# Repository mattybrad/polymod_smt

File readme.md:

# PolyMod SMT test

This will be a small polyphonic digital modular synthesizer, using a Teensy 3.2. The design is based on my tutorial from Hackspace magazine (issue 17), and was also featured in the Book of Making (volume 2). Currently this is a work in progress, so don't go ordering any PCBs just yet. This is really just a project for me to get some practice designing with surface-mount components and specifying for a pick-and-place machine, which I haven't done before.

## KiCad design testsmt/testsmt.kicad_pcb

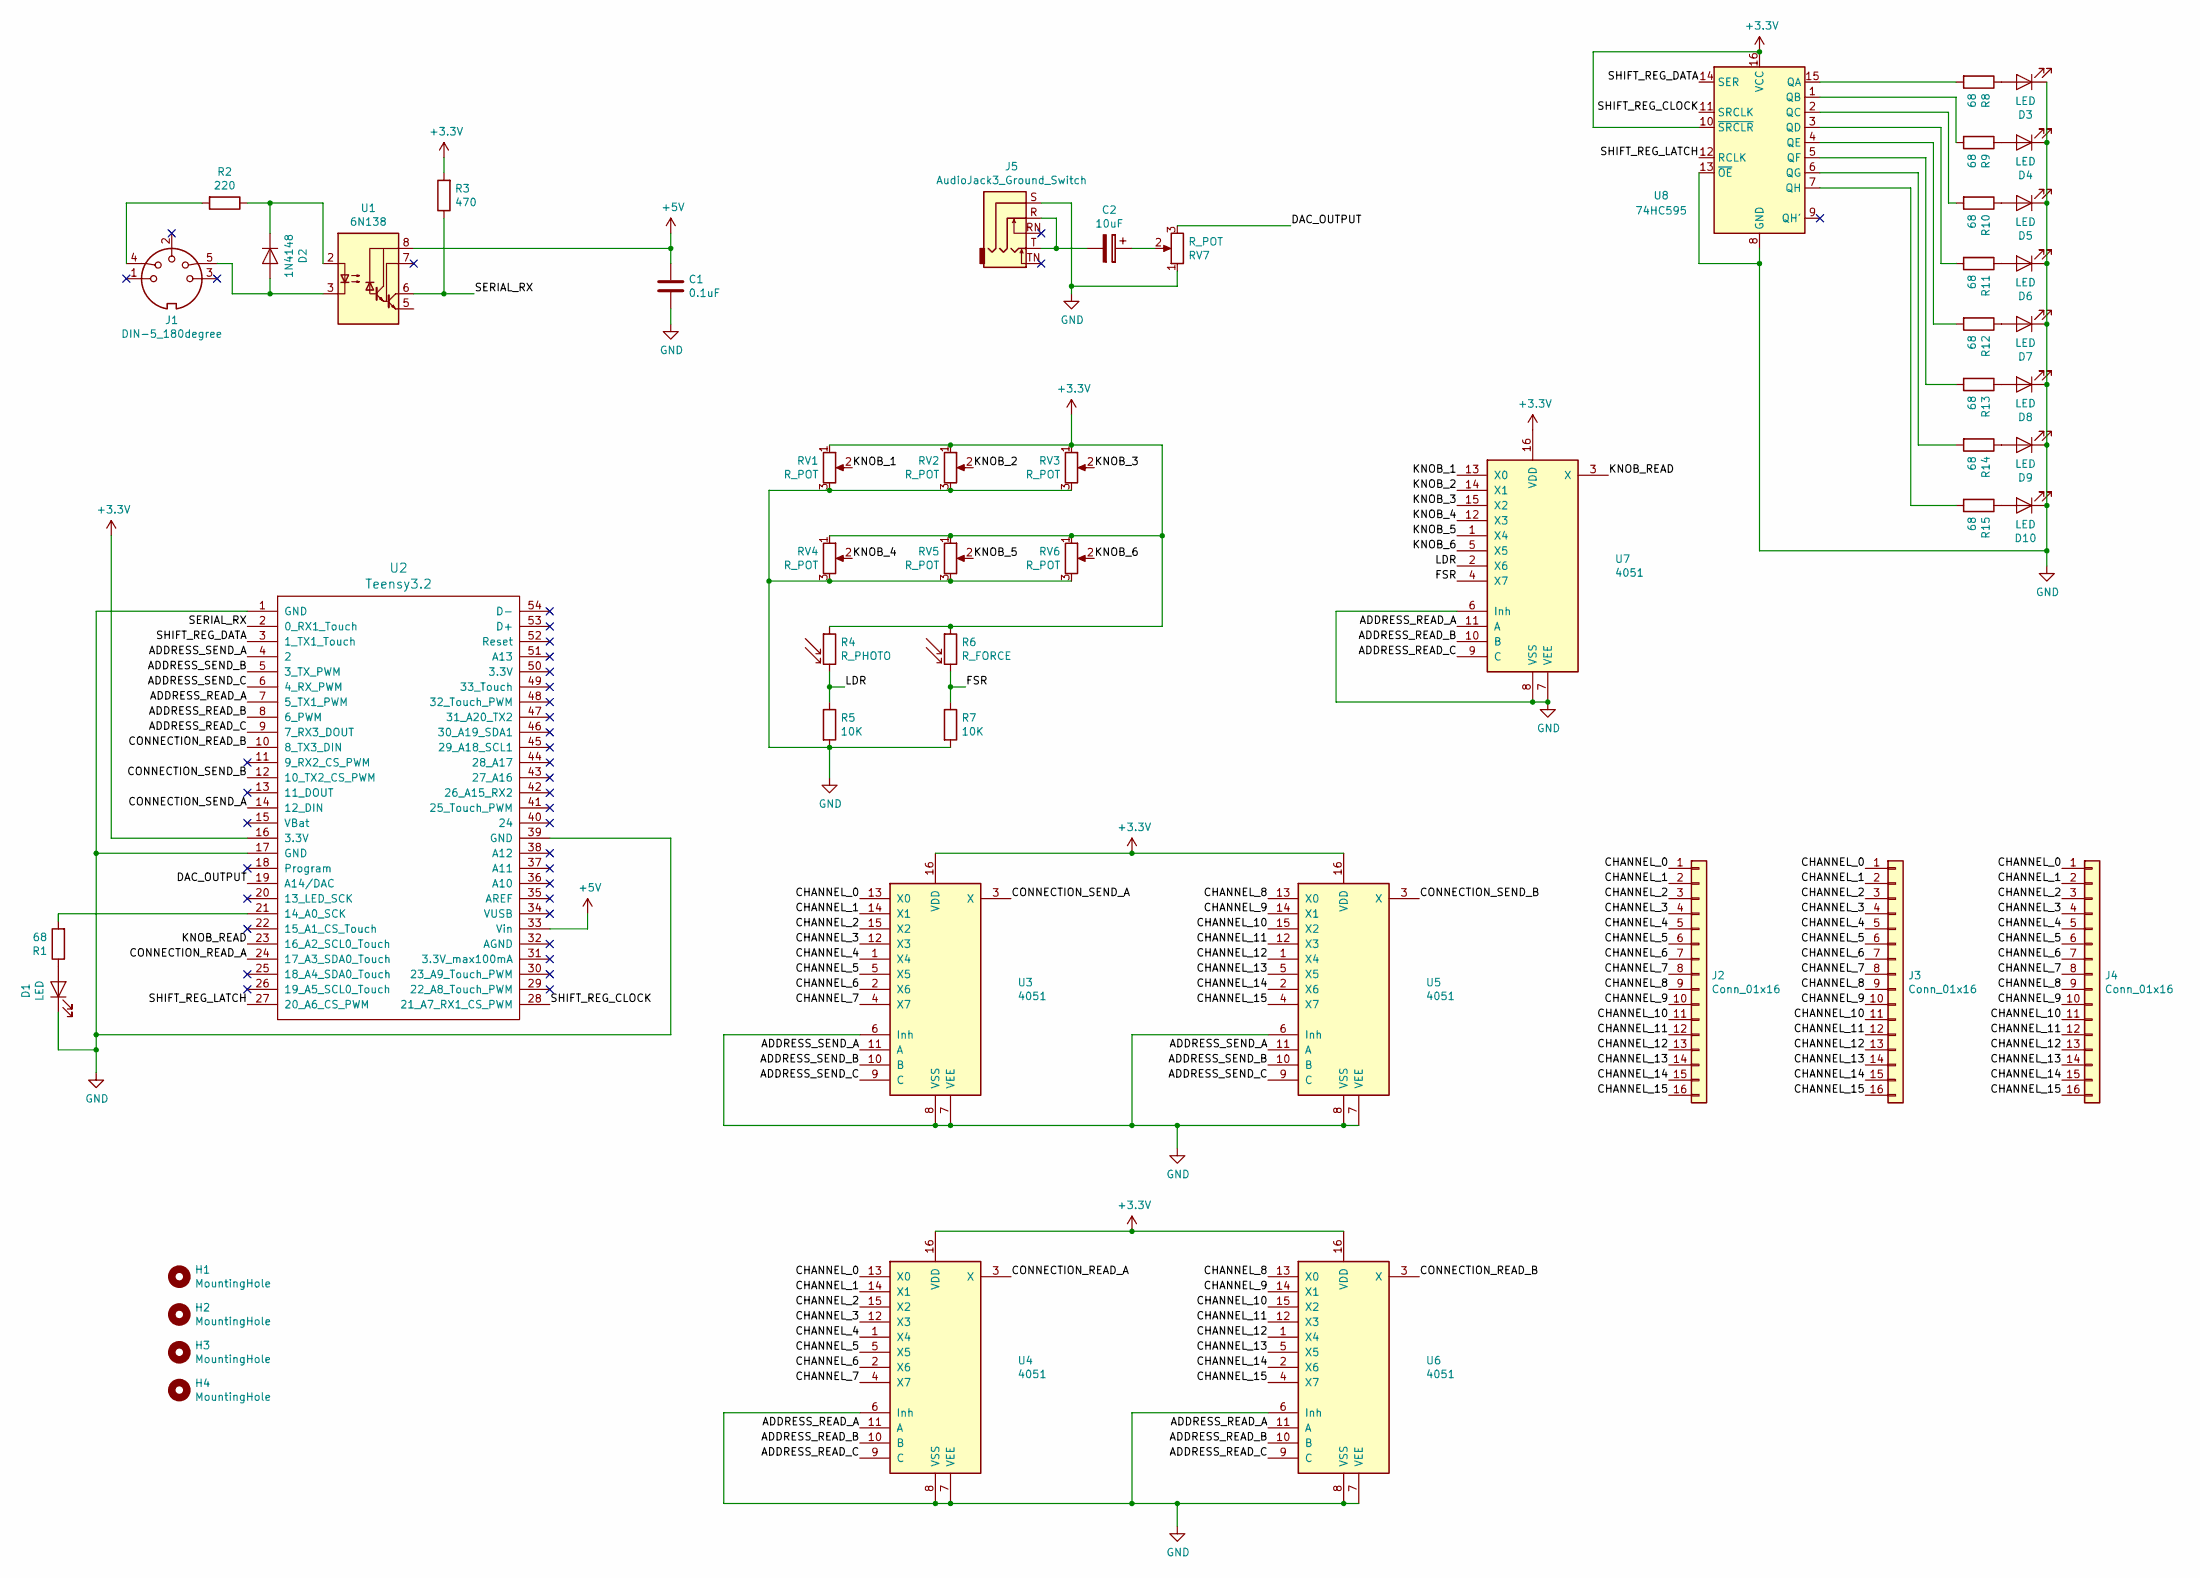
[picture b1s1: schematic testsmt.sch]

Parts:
C1: 0.1uF; C_0805_2012Metric
C2: 10uF; CP_EIA-3216-18_Kemet-A
D1, D3, D4, D5, D6, D7, D8, D9, D10: LED; LED_0805_2012Metric
D2: 1N4148; D_SOD-123
H1, H2, H3, H4: MountingHole; MountingHole_3.2mm_M3
J1: DIN-5_180degree; MIDI_DIN5
J2, J3, J4: Conn_01x16; PinSocket_1x16_P2.54mm_Vertical
J5: AudioJack3_Ground_Switch; Tayda_3.5mm_stereo_TRS_jack_A-853
R1, R8, R9, R10, R11, R12, R13, R14, R15: 68; R_0805_2012Metric
R2: 220; R_0805_2012Metric
R3: 470; R_0805_2012Metric
R4: R_PHOTO; PinHeader_1x02_P2.54mm_Vertical
R5, R7: 10K; R_0805_2012Metric
R6: R_FORCE; PinHeader_1x02_P2.54mm_Vertical
RV1, RV2, RV3, RV4, RV5, RV6, RV7: R_POT; Potentiometer_Alps_RK09K_Single_Vertical
U1: 6N138; SMDIP-8_W9.53mm
U2: Teensy3.2; Teensy30_31_32_LC
U3, U4, U5, U6, U7: 4051; SOIC-16_3.9x9.9mm_P1.27mm
U8: 74HC595; SOIC-16_3.9x9.9mm_P1.27mm

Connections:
+3V3: R3.2, R4.1, R6.1, RV1.1, RV2.1, RV3.1, RV4.1, RV5.1, RV6.1, U2.16 (3.3V), U3.16 (VDD), U4.16 (VDD), U5.16 (VDD), U6.16 (VDD), U7.16 (VDD), U8.10 (~SRCLR), U8.16 (VCC)
+5V: C1.1, U1.8 (VCC), U2.33 (Vin)
/ADDRESS_READ_A: U2.7 (5_TX1_PWM), U4.11 (A), U6.11 (A), U7.11 (A)
/ADDRESS_READ_B: U2.8 (6_PWM), U4.10 (B), U6.10 (B), U7.10 (B)
/ADDRESS_READ_C: U2.9 (7_RX3_DOUT), U4.9 (C), U6.9 (C), U7.9 (C)
/ADDRESS_SEND_A: U2.4 (2), U3.11 (A), U5.11 (A)
/ADDRESS_SEND_B: U2.5 (3_TX_PWM), U3.10 (B), U5.10 (B)
/ADDRESS_SEND_C: U2.6 (4_RX_PWM), U3.9 (C), U5.9 (C)
/CHANNEL_0: J2.1, J3.1, J4.1, U3.13 (X0), U4.13 (X0)
/CHANNEL_1: J2.2, J3.2, J4.2, U3.14 (X1), U4.14 (X1)
/CHANNEL_2: J2.3, J3.3, J4.3, U3.15 (X2), U4.15 (X2)
/CHANNEL_3: J2.4, J3.4, J4.4, U3.12 (X3), U4.12 (X3)
/CHANNEL_4: J2.5, J3.5, J4.5, U3.1 (X4), U4.1 (X4)
/CHANNEL_5: J2.6, J3.6, J4.6, U3.5 (X5), U4.5 (X5)
/CHANNEL_6: J2.7, J3.7, J4.7, U3.2 (X6), U4.2 (X6)
/CHANNEL_7: J2.8, J3.8, J4.8, U3.4 (X7), U4.4 (X7)
/CHANNEL_8: J2.9, J3.9, J4.9, U5.13 (X0), U6.13 (X0)
/CHANNEL_9: J2.10, J3.10, J4.10, U5.14 (X1), U6.14 (X1)
/CHANNEL_10: J2.11, J3.11, J4.11, U5.15 (X2), U6.15 (X2)
/CHANNEL_11: J2.12, J3.12, J4.12, U5.12 (X3), U6.12 (X3)
/CHANNEL_12: J2.13, J3.13, J4.13, U5.1 (X4), U6.1 (X4)
/CHANNEL_13: J2.14, J3.14, J4.14, U5.5 (X5), U6.5 (X5)
/CHANNEL_14: J2.15, J3.15, J4.15, U5.2 (X6), U6.2 (X6)
/CHANNEL_15: J2.16, J3.16, J4.16, U5.4 (X7), U6.4 (X7)
/CONNECTION_READ_A: U2.24 (17_A3_SDA0_Touch), U4.3 (X)
/CONNECTION_READ_B: U2.10 (8_TX3_DIN), U6.3 (X)
/CONNECTION_SEND_A: U2.14 (12_DIN), U3.3 (X)
/CONNECTION_SEND_B: U2.12 (10_TX2_CS_PWM), U5.3 (X)
/DAC_OUTPUT: RV7.3, U2.19 (A14/DAC)
/FSR: R6.2, R7.1, U7.4 (X7)
/KNOB_1: RV1.2, U7.13 (X0)
/KNOB_2: RV2.2, U7.14 (X1)
/KNOB_3: RV3.2, U7.15 (X2)
/KNOB_4: RV4.2, U7.12 (X3)
/KNOB_5: RV5.2, U7.1 (X4)
/KNOB_6: RV6.2, U7.5 (X5)
/KNOB_READ: U2.23 (16_A2_SCL0_Touch), U7.3 (X)
/LDR: R4.2, R5.1, U7.2 (X6)
/SERIAL_RX: R3.1, U1.6 (VO2), U2.2 (0_RX1_Touch)
/SHIFT_REG_CLOCK: U2.28 (21_A7_RX1_CS_PWM), U8.11 (SRCLK)
/SHIFT_REG_DATA: U2.3 (1_TX1_Touch), U8.14 (SER)
/SHIFT_REG_LATCH: U2.27 (20_A6_CS_PWM), U8.12 (RCLK)
GND: C1.2, D1.1 (K), D3.1 (K), D4.1 (K), D5.1 (K), D6.1 (K), D7.1 (K), D8.1 (K), D9.1 (K), D10.1 (K), J5.S, R5.2, R7.2, RV1.3, RV2.3, RV3.3, RV4.3, RV5.3, RV6.3, RV7.1, U2.1 (GND), U2.17 (GND), U2.39 (GND), U3.6 (Inh), U3.7 (VEE), U3.8 (VSS), U4.6 (Inh), U4.7 (VEE), U4.8 (VSS), U5.6 (Inh), U5.7 (VEE), U5.8 (VSS), U6.6 (Inh), U6.7 (VEE), U6.8 (VSS), U7.6 (Inh), U7.7 (VEE), U7.8 (VSS), U8.8 (GND), U8.13 (~OE)
unnamed: C2.1, RV7.2
unnamed: C2.2, J5.R, J5.T
unnamed: D1.2 (A), R1.1
unnamed: D2.1 (K), R2.1, U1.2 (C1)
unnamed: D2.2 (A), J1.5, U1.3 (C2)
unnamed: D3.2 (A), R8.1
unnamed: D4.2 (A), R9.1
unnamed: D5.2 (A), R10.1
unnamed: D6.2 (A), R11.1
unnamed: D7.2 (A), R12.1
unnamed: D8.2 (A), R13.1
unnamed: D9.2 (A), R14.1
unnamed: D10.2 (A), R15.1
unnamed: J1.4, R2.2
unnamed: R1.2, U2.21 (14_A0_SCK)
unnamed: R8.2, U8.15 (QA)
unnamed: R9.2, U8.1 (QB)
unnamed: R10.2, U8.2 (QC)
unnamed: R11.2, U8.3 (QD)
unnamed: R12.2, U8.4 (QE)
unnamed: R13.2, U8.5 (QF)
unnamed: R14.2, U8.6 (QG)
unnamed: R15.2, U8.7 (QH)

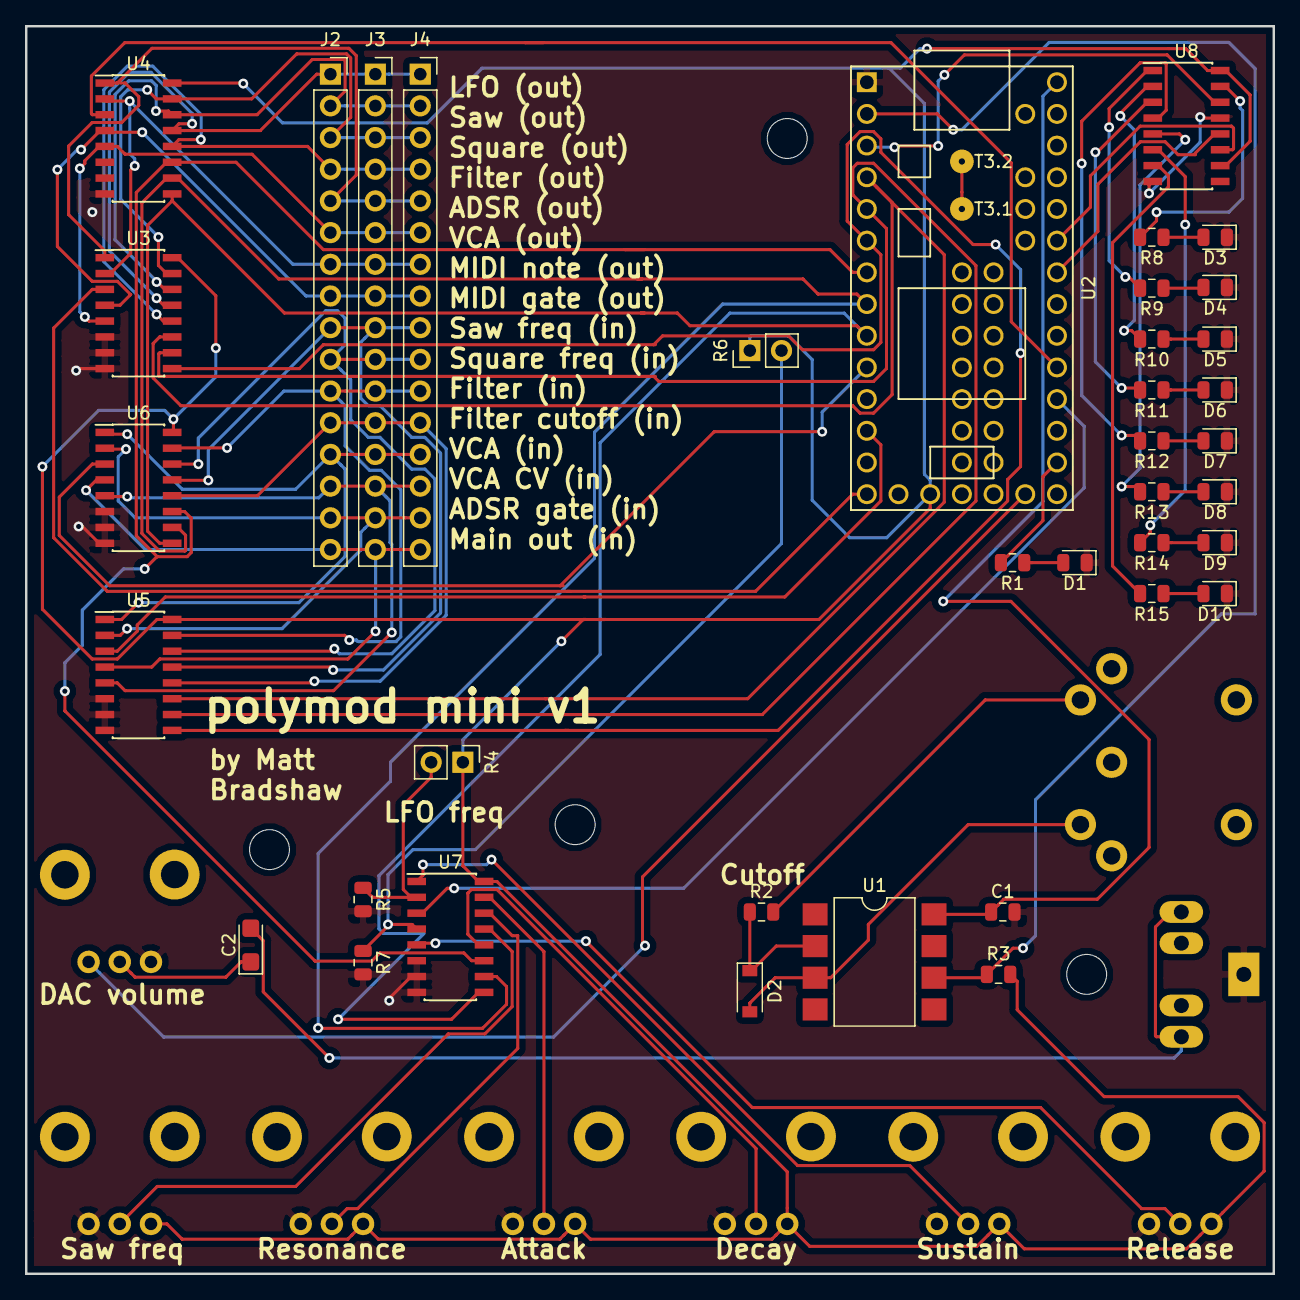
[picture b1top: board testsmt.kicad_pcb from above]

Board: 2 copper layers, 100.0 x 100.0 mm, 51 parts (0 on the bottom side), 66 nets.

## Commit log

2020-03-30 schematic nearly done
2020-03-30 schematic looking good
2020-03-30 added readme
2020-03-30 nearly done adding footprints
2020-03-30 footprints hopefully done
2020-03-30 started laying out board
2020-03-30 about to try out some routing
2020-03-30 started routing
2020-03-30 routing going well
2020-03-31 routing...
2020-03-31 more routing...
2020-03-31 think the hard routing is done...?
2020-03-31 computer keeps crashing
2020-04-01 moving things
2020-04-01 fsr in place
2020-04-01 pretty happy with layout
2020-04-01 routing routing routing
2020-04-01 13 unrouted left
2020-04-01 where is the last unrouted connection?!
2020-04-01 routing done
2020-04-01 nearly there
2020-04-01 mounting holes
2020-04-01 gerbers etc, and manually fixed rotations
2020-04-01 fixed rotations again, apparently they go anticlockwise
2020-04-01 pcbs ordered!
